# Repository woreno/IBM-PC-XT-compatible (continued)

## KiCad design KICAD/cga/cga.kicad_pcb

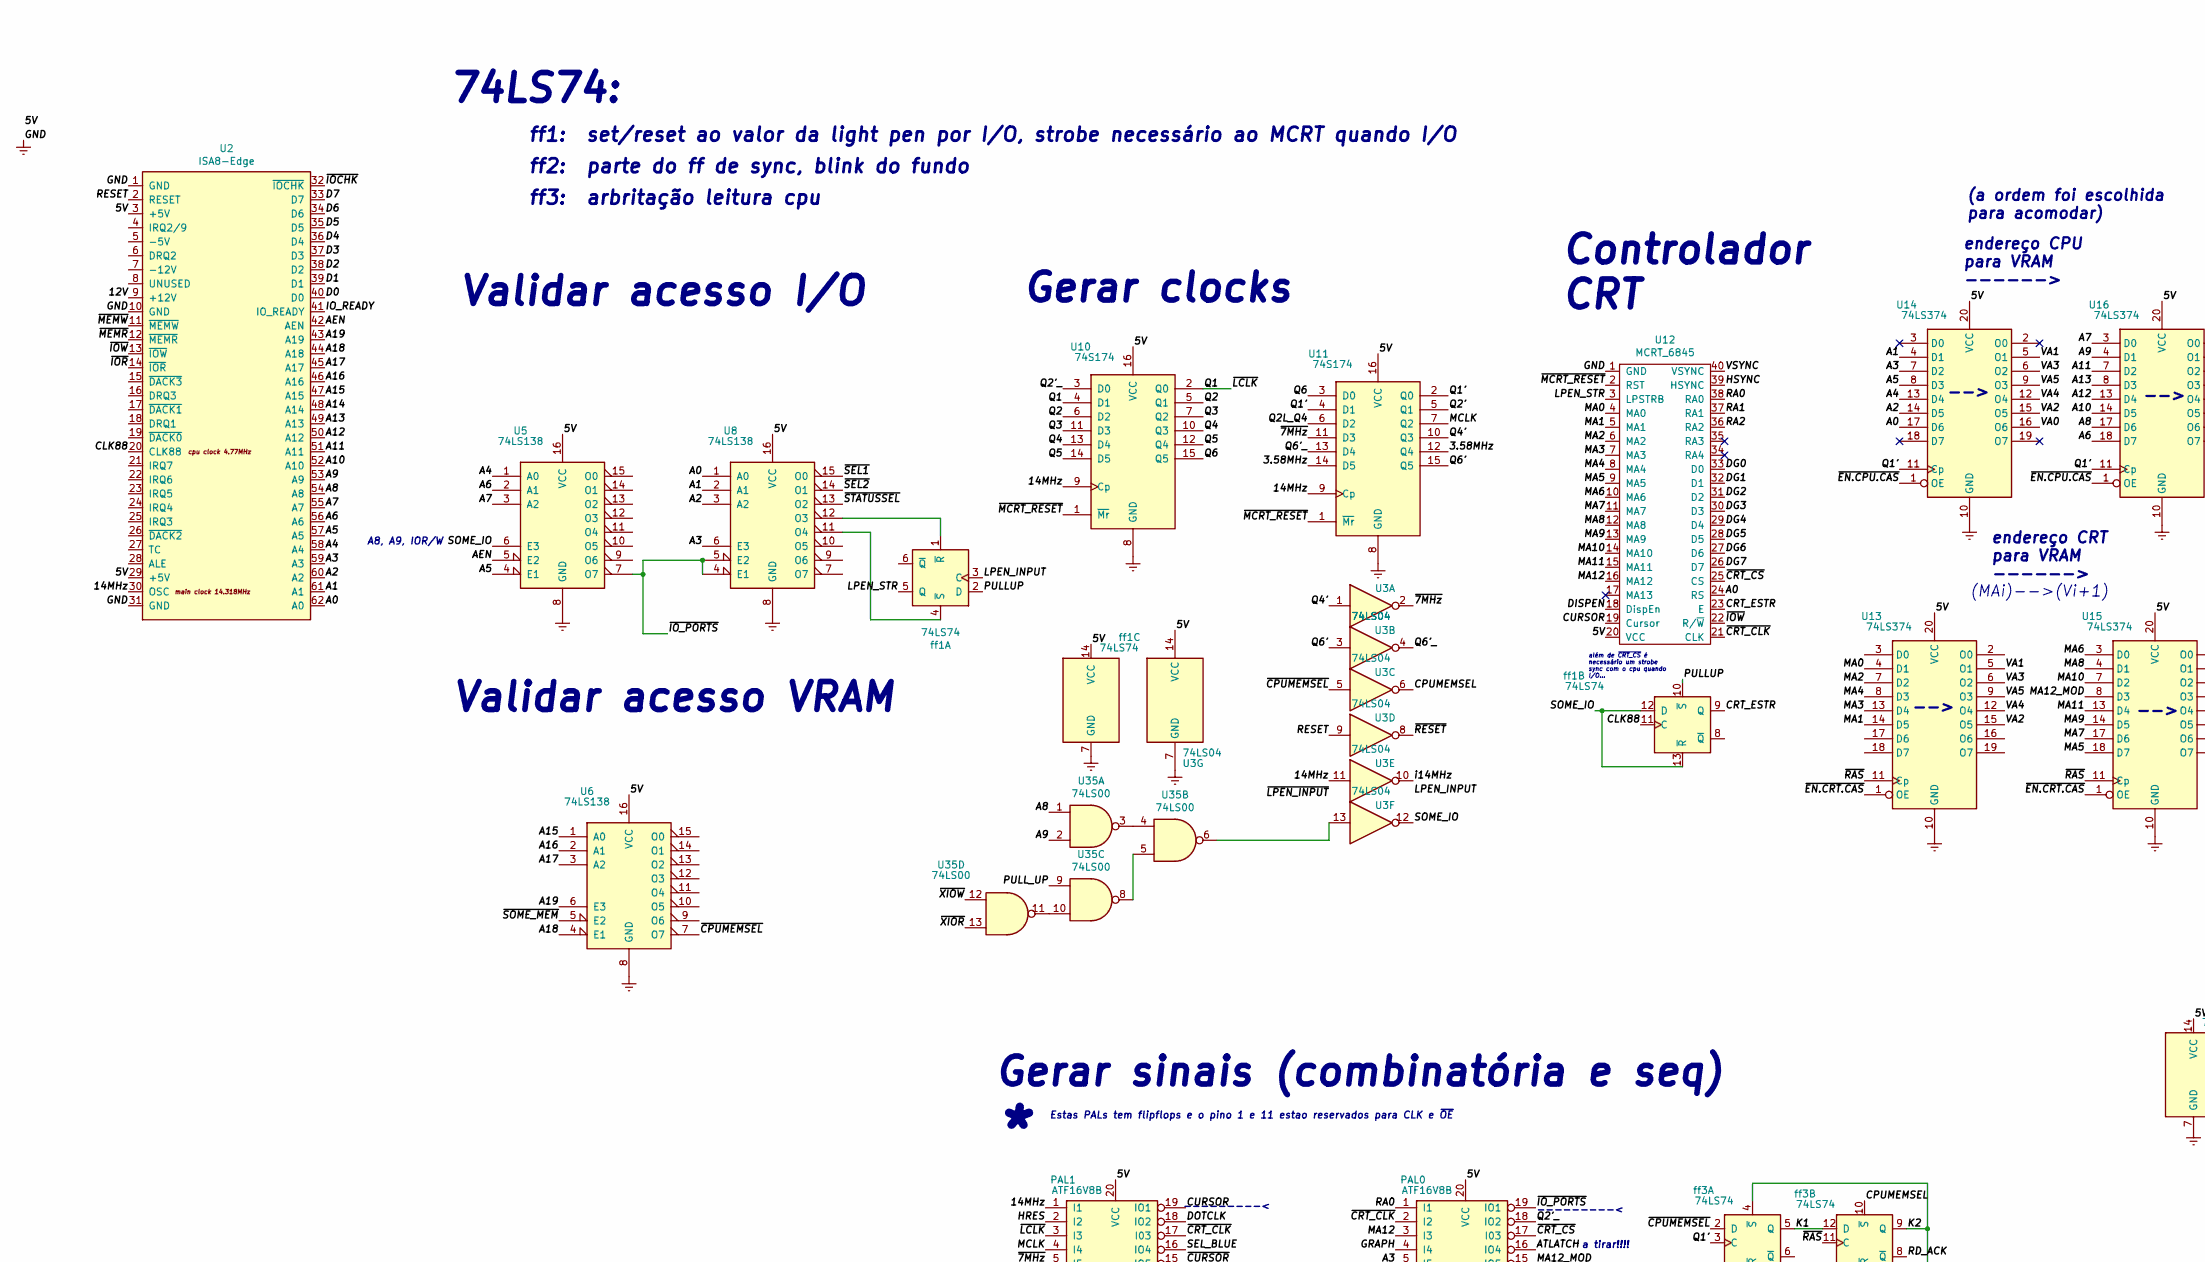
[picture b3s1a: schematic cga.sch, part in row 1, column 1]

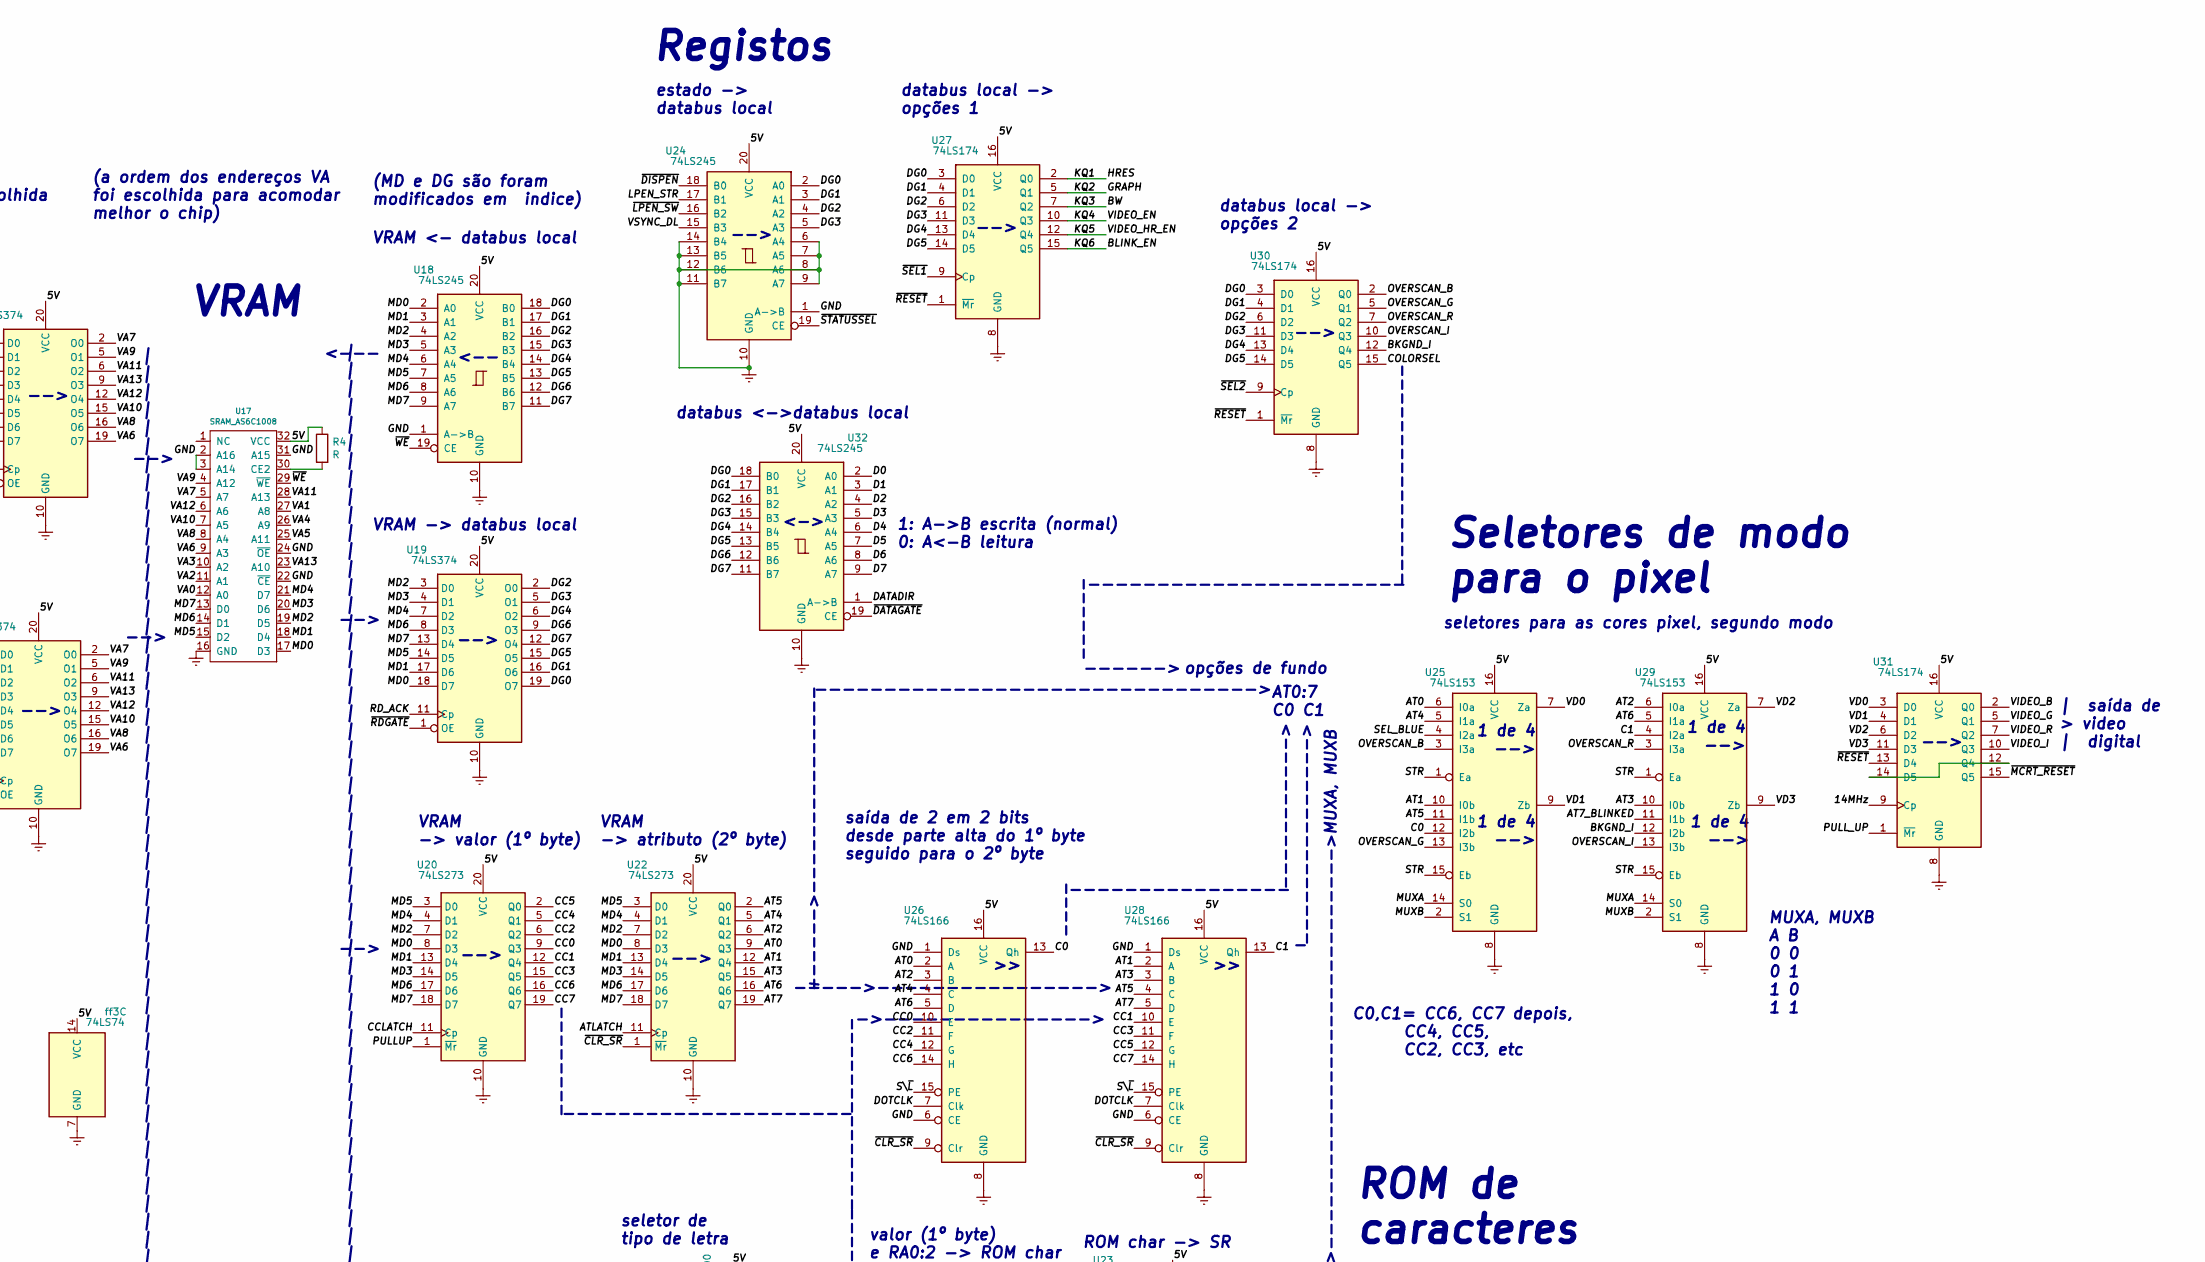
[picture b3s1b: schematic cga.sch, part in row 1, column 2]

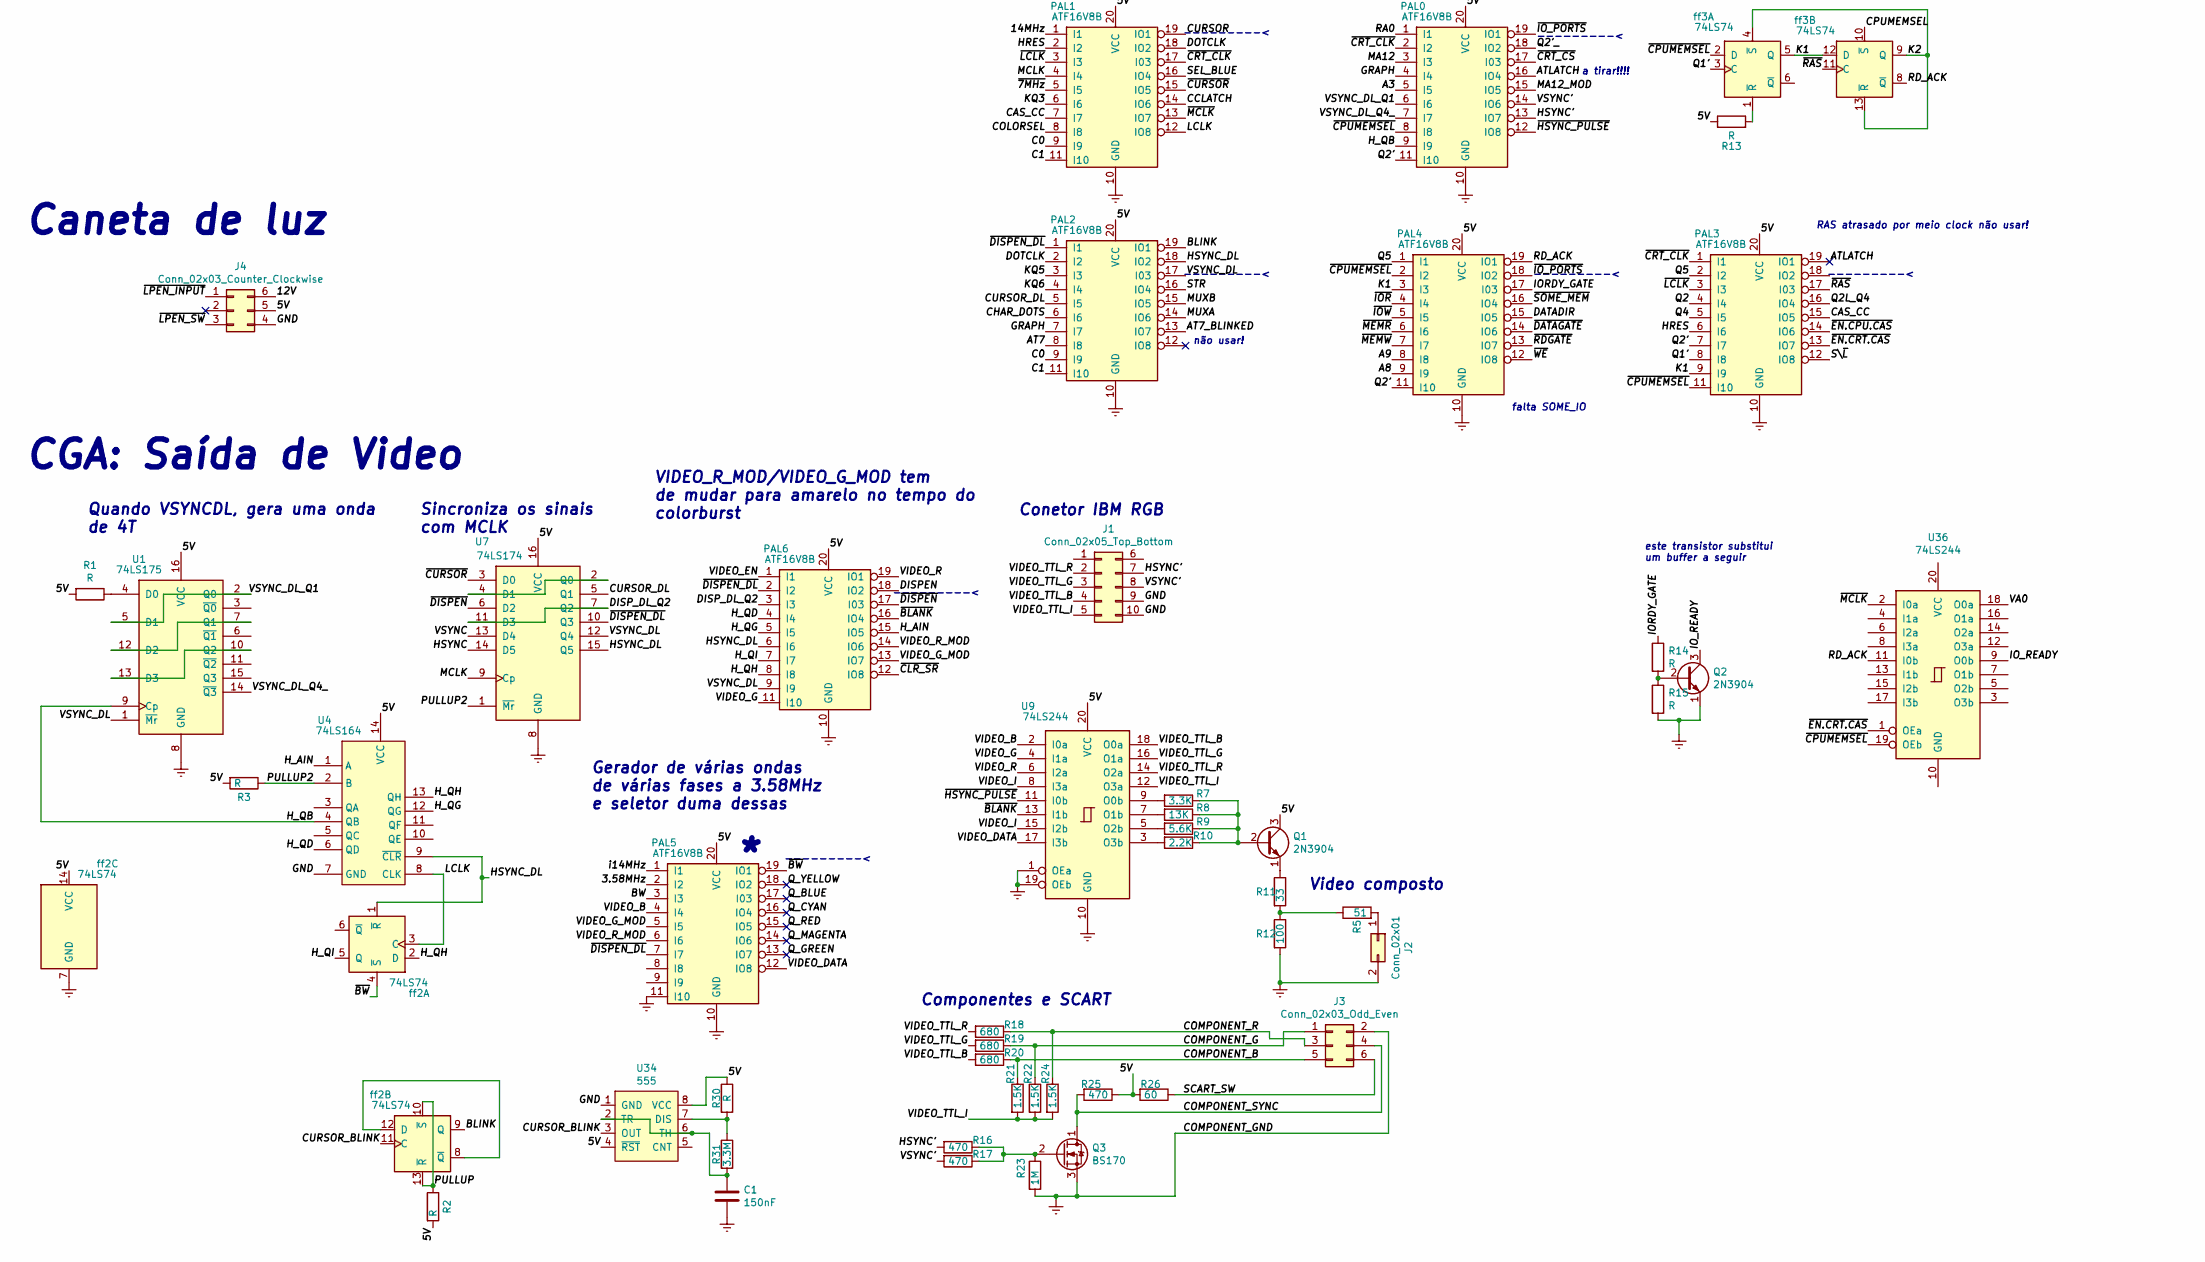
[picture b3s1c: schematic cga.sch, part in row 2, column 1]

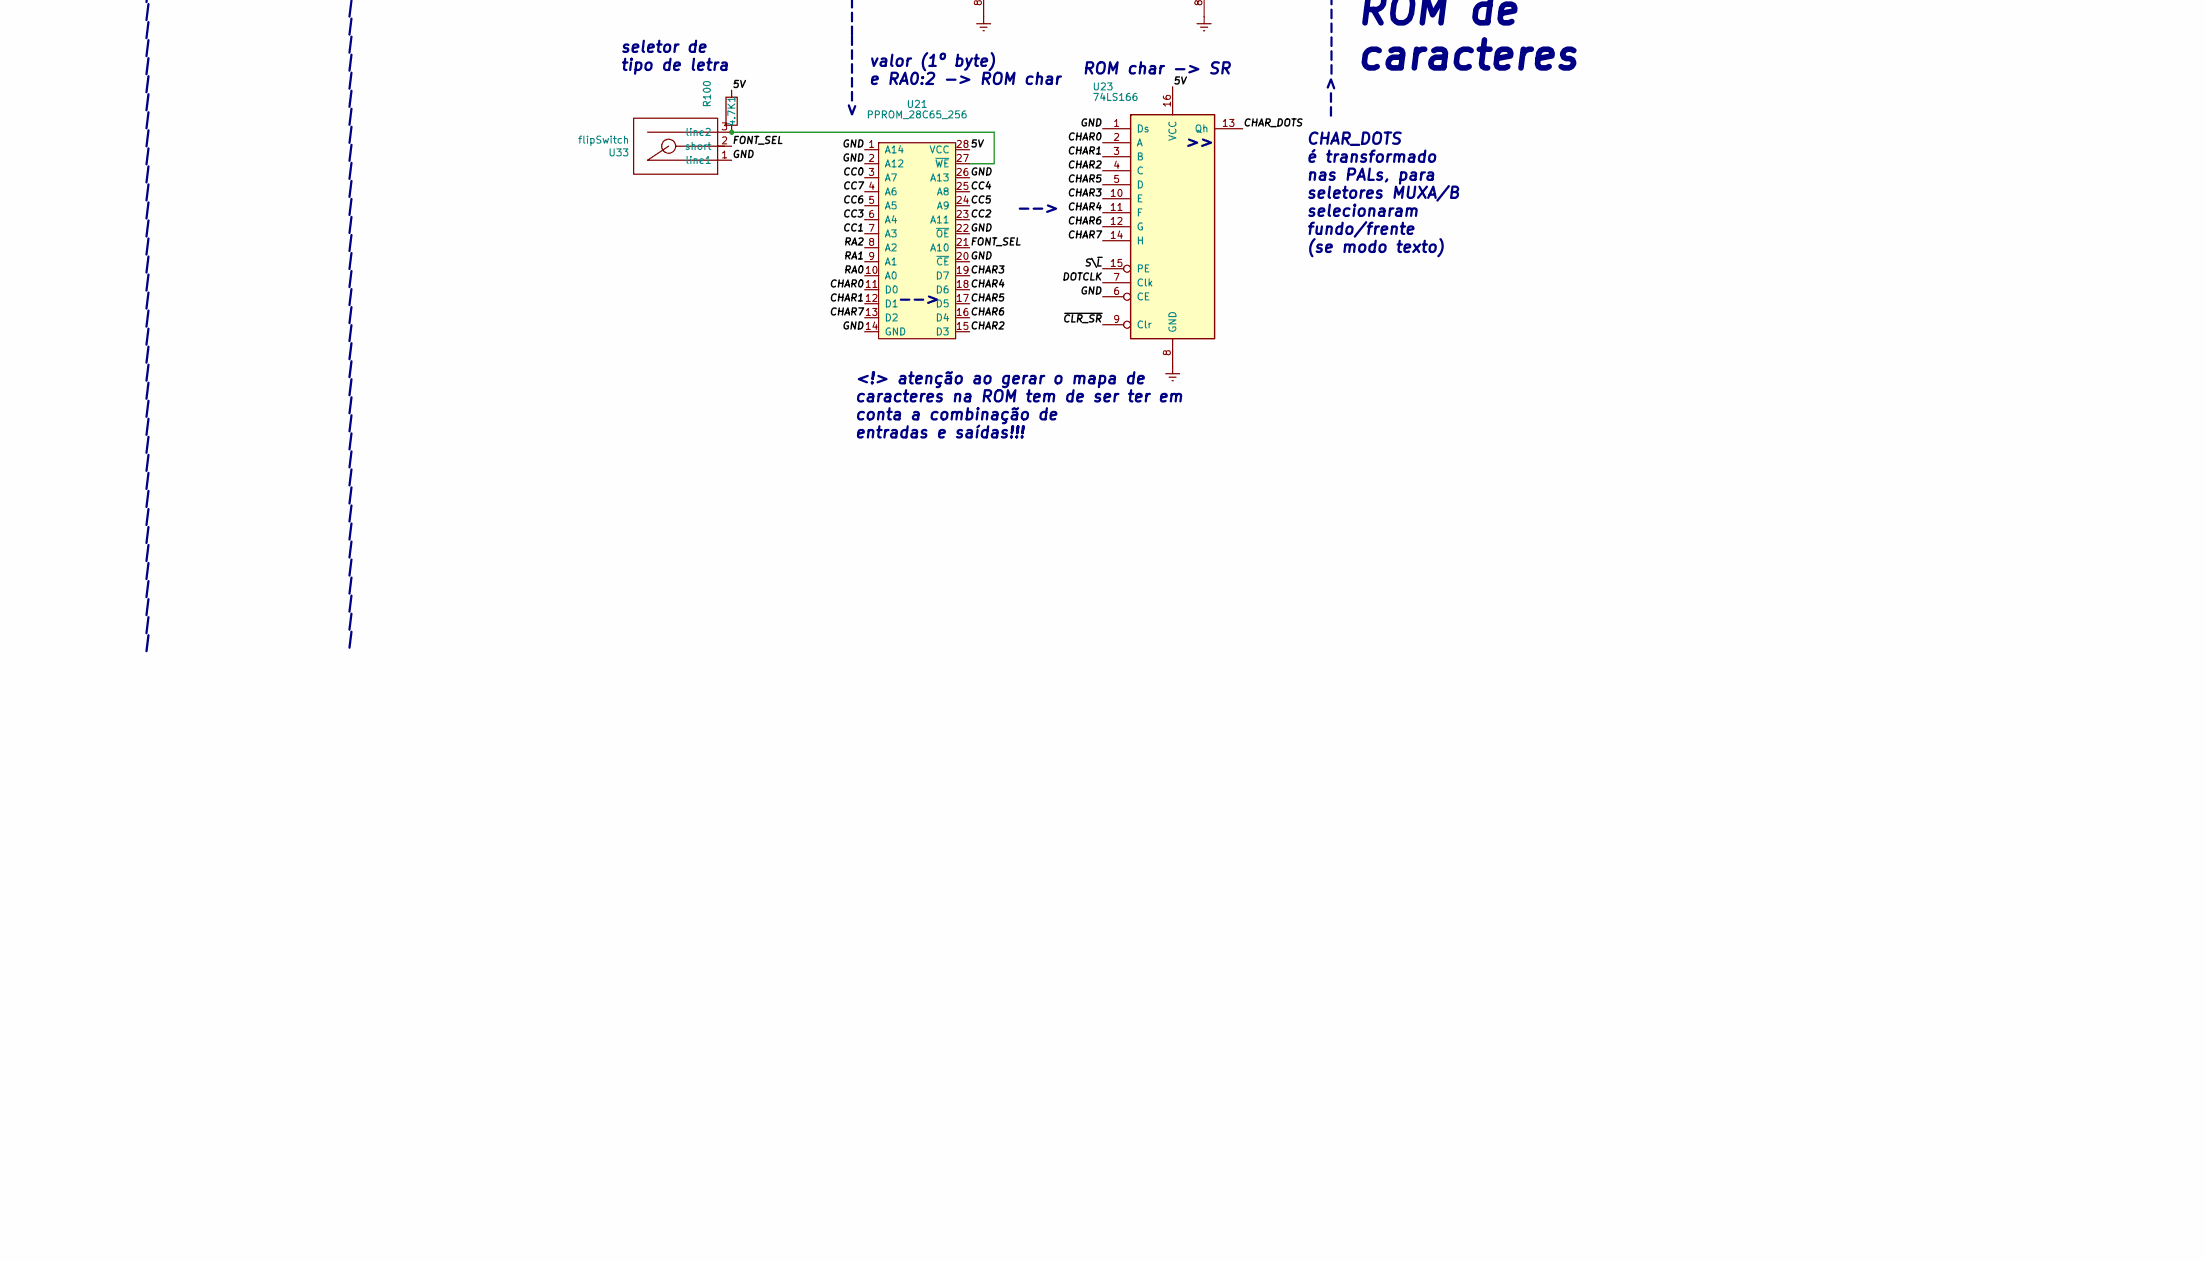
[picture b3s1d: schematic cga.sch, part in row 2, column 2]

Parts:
4.7K1: R100; standard_2pins
C1: 150nF; standard_2pins_half
J1: Conn_02x05_Top_Bottom; conetor_2x05_P2.54_toDB9
J2: Conn_02x01; jumper_set_1
J3: Conn_02x03_Odd_Even; jumper_set_3
J4: Conn_02x03_Counter_Clockwise; jumper_set_3
PAL0, PAL1, PAL2, PAL3, PAL4, PAL5, PAL6: ATF16V8B; standard_DIP_20pins_thin_body
Q1, Q2: 2N3904; TO-92_Inline
Q3: BS170; TO-92_Inline
R1, R2, R3, R4, R13, R14, R15, R30: R; standard_2pins
R5: 51; standard_2pins
R7: 3.3K; standard_2pins
R8: 13K; standard_2pins
R9: 5.6K; standard_2pins
R10: 2.2K; standard_2pins
R11: 33; standard_2pins
R12: 100; standard_2pins
R16, R17, R25: 470; standard_2pins
R18, R19, R20: 680; standard_2pins
R21, R22, R24: 1.5K; standard_2pins
R23: 1M; standard_2pins
R26: 60; standard_2pins
R31: 3.3M; standard_2pins
U1: 74LS175; standard_DIP_16OvalPins
U2: ISA8-Edge; ISA_8bit_edge
U3: 74LS04; standard_DIP_14OvalPins
U4: 74LS164; standard_DIP_14OvalPins
U5, U6, U8: 74LS138; standard_DIP_16OvalPins
U7, U27, U30, U31: 74LS174; standard_DIP_16OvalPins
U9, U36: 74LS244; standard_DIP_20pins_thin_body
U10, U11: 74S174; standard_DIP_16OvalPins
U12: MCRT_6845; standard_DIP_40pins_doubleBody_thinpins
U13, U14, U15, U16, U19: 74LS374; standard_DIP_20pins_thin_body
U17: SRAM_AS6C1008; standard_DIP_32pins_thin_doubleBody
U18, U24, U32: 74LS245; standard_DIP_20pins_thin_body
U20, U22: 74LS273; standard_DIP_20pins_thin_body
U21: PPROM_28C65_256; standard_DIP_28pins_thin_doubleBody
U23, U26, U28: 74LS166; standard_DIP_16OvalPins
U25, U29: 74LS153; standard_DIP_16OvalPins
U33: flipSwitch; mini_flipswitch2.54
U34: 555; standard_DIP_8pins
U35: 74LS00; standard_DIP_14OvalPins
ff1, ff2, ff3: 74LS74; standard_DIP_14OvalPins

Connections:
/3.58MHz: PAL5.2 (I2), U11.12 (Q4), U11.14 (D5)
/5V: 4.7K1.1, J4.5, PAL0.20 (VCC), PAL1.20 (VCC), PAL2.20 (VCC), PAL3.20 (VCC), PAL4.20 (VCC), PAL5.20 (VCC), PAL6.20 (VCC), Q1.3 (C), R1.2, R2.2, R3.2, R4.1, R13.1, R25.1, R26.2, R30.1, U1.16 (VCC), U2.3 (+5V), U2.29 (+5V), U3.14 (VCC), U4.14 (VCC), U5.16 (VCC), U6.16 (VCC), U7.16 (VCC), U8.16 (VCC), U9.20 (VCC), U10.16 (VCC), U11.16 (VCC), U12.20 (VCC), U13.20 (VCC), U14.20 (VCC), U15.20 (VCC), U16.20 (VCC), U17.32 (VCC), U18.20 (VCC), U19.20 (VCC), U20.20 (VCC), U21.28 (VCC), U22.20 (VCC), U23.16 (VCC), U24.20 (VCC), U25.16 (VCC), U26.16 (VCC), U27.16 (VCC), U28.16 (VCC), U29.16 (VCC), U30.16 (VCC), U31.16 (VCC), U32.20 (VCC), U34.4 (~RST), U34.8 (VCC), ff1.14 (VCC), ff2.14 (VCC), ff3.14 (VCC); also elsewhere on the board
/12V: J4.6, U2.9 (+12V)
/14MHz: PAL1.1 (I1), U2.30 (OSC), U3.11, U10.9 (Cp), U11.9 (Cp), U31.9 (Cp)
/A0: U2.62 (A0), U8.1 (A0), U12.24 (RS), U14.17 (D6)
/A1: U2.61 (A1), U8.2 (A1), U14.4 (D1)
/A2: U2.60 (A2), U8.3 (A2), U14.14 (D5)
/A3: PAL0.5 (I5), U2.59 (A3), U8.6 (E3), U14.7 (D2)
/A4: U2.58 (A4), U5.1 (A0), U14.13 (D4)
/A5: U2.57 (A5), U5.4 (E1), U14.8 (D3)
/A6: U2.56 (A6), U5.2 (A1), U16.18 (D7)
/A7: U2.55 (A7), U5.3 (A2), U16.3 (D0)
/A8: PAL4.9 (I9), U2.54 (A8), U16.17 (D6), U35.1
/A9: PAL4.8 (I8), U2.53 (A9), U16.4 (D1), U35.2
/A10: U2.52 (A10), U16.14 (D5)
/A11: U2.51 (A11), U16.7 (D2)
/A12: U2.50 (A12), U16.13 (D4)
/A13: U2.49 (A13), U16.8 (D3)
/A14: U2.48 (A14)
/A15: U2.47 (A15), U6.1 (A0)
/A16: U2.46 (A16), U6.2 (A1)
/A17: U2.45 (A17), U6.3 (A2)
/A18: U2.44 (A18), U6.4 (E1)
/A19: U2.43 (A19), U6.6 (E3)
/AEN: U2.42 (AEN), U5.5 (E2)
/AT0: U22.9 (Q3), U25.6 (I0a), U26.2 (A)
/AT1: U22.12 (Q4), U25.10 (I0b), U28.2 (A)
/AT2: U22.6 (Q2), U26.3 (B), U29.6 (I0a)
/AT3: U22.15 (Q5), U28.3 (B), U29.10 (I0b)
/AT4: U22.5 (Q1), U25.5 (I1a), U26.4 (C)
/AT5: U22.2 (Q0), U25.11 (I1b), U28.4 (C)
/AT6: U22.16 (Q6), U26.5 (D), U29.5 (I1a)
/AT7: PAL2.8 (I8), U22.19 (Q7), U28.5 (D)
/AT7_BLINKED: PAL2.13 (IO7), U29.11 (I1b)
/ATLATCH: PAL0.16 (IO4), PAL3.19 (IO1), U22.11 (Cp)
/BKGND_I: U29.12 (I2b), U30.12 (Q4)
/BLINK: PAL2.19 (IO1), ff2.9 (Q)
/BLINK_EN: PAL2.4 (I4), U27.15 (Q5)
/BW: PAL1.6 (I6), PAL5.3 (I3), U27.7 (Q2)
/C0: PAL1.9 (I9), PAL2.9 (I9), U25.12 (I2b), U26.13 (Qh)
/C1: PAL1.11 (I10), PAL2.11 (I10), U28.13 (Qh), U29.4 (I2a)
/CAS_CC: PAL1.7 (I7), PAL3.15 (IO5)
/CC0: U20.9 (Q3), U21.3 (A7), U26.10 (E)
/CC1: U20.12 (Q4), U21.7 (A3), U28.10 (E)
/CC2: U20.6 (Q2), U21.23 (A11), U26.11 (F)
/CC3: U20.15 (Q5), U21.6 (A4), U28.11 (F)
/CC4: U20.5 (Q1), U21.25 (A8), U26.12 (G)
/CC5: U20.2 (Q0), U21.24 (A9), U28.12 (G)
/CC6: U20.16 (Q6), U21.5 (A5), U26.14 (H)
/CC7: U20.19 (Q7), U21.4 (A6), U28.14 (H)
/CCLATCH: PAL1.14 (IO6), U20.11 (Cp)
/CHAR0: U21.11 (D0), U23.2 (A)
/CHAR1: U21.12 (D1), U23.3 (B)
/CHAR2: U21.15 (D3), U23.4 (C)
/CHAR3: U21.19 (D7), U23.10 (E)
/CHAR4: U21.18 (D6), U23.11 (F)
/CHAR5: U21.17 (D5), U23.5 (D)
/CHAR6: U21.16 (D4), U23.12 (G)
/CHAR7: U21.13 (D2), U23.14 (H)
/CHAR_DOTS: PAL2.6 (I6), U23.13 (Qh)
/CLK88: U2.20 (CLK88), ff1.11 (C)
/COLORSEL: PAL1.8 (I8), U30.15 (Q5)
/COMPONENT_B: J3.5, R20.1, R21.1
/COMPONENT_G: J3.1, R19.1, R22.1
/COMPONENT_R: J3.3, R18.1, R24.1
/COMPONENT_SYNC: J3.4, Q3.1 (D), R25.2
/CPUMEMSEL: U3.6, ff3.10 (~S)
/CRT_ESTR: U12.23 (E), ff1.9 (Q)
/CURSOR: PAL1.19 (IO1), U12.19 (Cursor)
/CURSOR_BLINK: U34.3 (OUT), ff2.11 (C)
/CURSOR_DL: PAL2.5 (I5), U7.5 (Q1)
/D0: U2.40 (D0), U32.2 (A0)
/D1: U2.39 (D1), U32.3 (A1)
/D2: U2.38 (D2), U32.4 (A2)
/D3: U2.37 (D3), U32.5 (A3)
/D4: U2.36 (D4), U32.6 (A4)
/D5: U2.35 (D5), U32.7 (A5)
/D6: U2.34 (D6), U32.8 (A6)
/D7: U2.33 (D7), U32.9 (A7)
/DATADIR: PAL4.15 (IO5), U32.1 (A->B)
/DG0: U12.33 (D0), U18.18 (B0), U19.19 (O7), U24.2 (A0), U27.3 (D0), U30.3 (D0), U32.18 (B0)
/DG1: U12.32 (D1), U18.17 (B1), U19.16 (O6), U24.3 (A1), U27.4 (D1), U30.4 (D1), U32.17 (B1)
/DG2: U12.31 (D2), U18.16 (B2), U19.2 (O0), U24.4 (A2), U27.6 (D2), U30.6 (D2), U32.16 (B2)
/DG3: U12.30 (D3), U18.15 (B3), U19.5 (O1), U24.5 (A3), U27.11 (D3), U30.11 (D3), U32.15 (B3)
/DG4: U12.29 (D4), U18.14 (B4), U19.6 (O2), U27.13 (D4), U30.13 (D4), U32.14 (B4)
/DG5: U12.28 (D5), U18.13 (B5), U19.15 (O5), U27.14 (D5), U30.14 (D5), U32.13 (B5)
/DG6: U12.27 (D6), U18.12 (B6), U19.9 (O3), U32.12 (B6)
/DG7: U12.26 (D7), U18.11 (B7), U19.12 (O4), U32.11 (B7)
/DISPEN: PAL6.18 (IO2), U12.18 (DispEn)
/DISP_DL_Q2: PAL6.3 (I3), U7.7 (Q2), U7.11 (D3)
/DOTCLK: PAL1.18 (IO2), PAL2.2 (I2), U23.7 (Clk), U26.7 (Clk), U28.7 (Clk)
/FONT_SEL: U21.21 (A10), U33.2 (short)
/GRAPH: PAL0.4 (I4), PAL2.7 (I7), U27.5 (Q1)
/HRES: PAL1.2 (I2), PAL3.6 (I6), U27.2 (Q0)
/HSYNC: U7.14 (D5), U12.39 (HSYNC)
/HSYNC': J1.7, PAL0.13 (IO7), R16.2
/HSYNC_DL: PAL2.18 (IO2), PAL6.6 (I6), U4.9 (~CLR), U7.15 (Q5), ff2.1 (~R)
/H_AIN: PAL6.15 (IO5), U4.1 (A)
/H_QB: PAL0.9 (I9), U1.9 (Cp), U4.4 (QB)
/H_QD: PAL6.4 (I4), U4.6 (QD)
/H_QG: PAL6.5 (I5), U4.12 (QG)
/H_QH: PAL6.8 (I8), U4.13 (QH), ff2.2 (D)
/H_QI: PAL6.7 (I7), ff2.5 (Q)
/IORDY_GATE: PAL4.17 (I03), R14.1
/IO_READY: Q2.3 (C), U2.41 (IO_READY), U36.9 (O0b)
/K1: PAL3.9 (I9), PAL4.3 (I3), ff3.5 (Q), ff3.12 (D)
/K2: ff3.4 (~S), ff3.9 (Q), ff3.13 (~R)
/KQ4: PAL6.1 (I1), U27.10 (Q3)
/KQ5: PAL2.3 (I3), U27.12 (Q4)
/LCLK: PAL1.12 (IO8), U4.8 (CLK), ff2.3 (C)
/LPEN_INPUT: ff1.3 (C)
/LPEN_STR: U12.3 (LPSTRB), U24.17 (B1), ff1.5 (Q)
/MA0: U12.4 (MA0), U13.4 (D1)
/MA1: U12.5 (MA1), U13.14 (D5)
/MA2: U12.6 (MA2), U13.7 (D2)
/MA3: U12.7 (MA3), U13.13 (D4)
/MA4: U12.8 (MA4), U13.8 (D3)
/MA5: U12.9 (MA5), U15.18 (D7)
/MA6: U12.10 (MA6), U15.3 (D0)
/MA7: U12.11 (MA7), U15.17 (D6)
/MA8: U12.12 (MA8), U15.4 (D1)
/MA9: U12.13 (MA9), U15.14 (D5)
/MA10: U12.14 (MA10), U15.7 (D2)
/MA11: U12.15 (MA11), U15.13 (D4)
/MA12: PAL0.3 (I3), U12.16 (MA12)
/MA12_MOD: PAL0.15 (IO5), U15.8 (D3)
/MCLK: PAL1.4 (I4), U7.9 (Cp), U11.7 (Q2)
/MD0: U17.17 (D3), U18.2 (A0), U19.18 (D7), U20.8 (D3), U22.8 (D3)
/MD1: U17.18 (D4), U18.3 (A1), U19.17 (D6), U20.13 (D4), U22.13 (D4)
/MD2: U17.19 (D5), U18.4 (A2), U19.3 (D0), U20.7 (D2), U22.7 (D2)
/MD3: U17.20 (D6), U18.5 (A3), U19.4 (D1), U20.14 (D5), U22.14 (D5)
/MD4: U17.21 (D7), U18.6 (A4), U19.7 (D2), U20.4 (D1), U22.4 (D1)
/MD5: U17.15 (D2), U18.7 (A5), U19.14 (D5), U20.3 (D0), U22.3 (D0)
/MD6: U17.14 (D1), U18.8 (A6), U19.8 (D3), U20.17 (D6), U22.17 (D6)
/MD7: U17.13 (D0), U18.9 (A7), U19.13 (D4), U20.18 (D7), U22.18 (D7)
/MUXA: PAL2.14 (IO6), U25.14 (S0), U29.14 (S0)
/MUXB: PAL2.15 (IO5), U25.2 (S1), U29.2 (S1)
/OVERSCAN_B: U25.3 (I3a), U30.2 (Q0)
/OVERSCAN_G: U25.13 (I3b), U30.5 (Q1)
/OVERSCAN_I: U29.13 (I3b), U30.10 (Q3)
/OVERSCAN_R: U29.3 (I3a), U30.7 (Q2)
/PULLUP: R2.1, U20.1 (~Mr), ff1.2 (D), ff1.10 (~S), ff2.10 (~S), ff2.13 (~R)
/PULLUP2: R3.1, U4.2 (B), U7.1 (~Mr)
/PULL_UP: U31.1 (~Mr), U35.9
/Q1: PAL1.3 (I3), PAL3.3 (I3), U10.2 (Q0), U10.4 (D1)
/Q1': PAL3.8 (I8), U11.2 (Q0), U11.4 (D1), U14.11 (Cp), U16.11 (Cp), ff3.3 (C)
/Q2: PAL3.4 (I4), U10.5 (Q1), U10.6 (D2)
/Q2': PAL0.11 (I10), PAL3.7 (I7), PAL4.11 (I10), U11.5 (Q1)
/Q2'_: PAL0.18 (IO2), U10.3 (D0)
/Q2L_Q4: PAL3.16 (IO4), U11.6 (D2)
/Q3: U10.7 (Q2), U10.11 (D3)
/Q4: PAL3.5 (I5), U10.10 (Q3), U10.13 (D4)
/Q4': U3.1, U11.10 (Q3)
/Q5: PAL3.2 (I2), PAL4.1 (I1), U10.12 (Q4), U10.14 (D5)
/Q6: U10.15 (Q5), U11.3 (D0)
/Q6': U3.3, U11.15 (Q5)
/Q6'_: U3.4, U11.13 (D4)
/Q_BLUE: PAL5.17 (I03)
/Q_CYAN: PAL5.16 (IO4)
/Q_GREEN: PAL5.13 (IO7)
/Q_MAGENTA: PAL5.14 (IO6)
/Q_RED: PAL5.15 (IO5)
/Q_YELLOW: PAL5.18 (IO2)
/RA0: PAL0.1 (I1), U12.38 (RA0), U21.10 (A0)
/RA1: U12.37 (RA1), U21.9 (A1)
/RA2: U12.36 (RA2), U21.8 (A2)
/RD_ACK: PAL4.19 (IO1), U19.11 (Cp), U36.11 (I0b), ff3.8 (~Q)
/RESET: U2.2 (RESET), U3.9
/SCART_SW: J3.6, R26.1
/SEL_BLUE: PAL1.16 (IO4), U25.4 (I2a)
/SOME_IO: U3.12, U5.6 (E3), ff1.12 (D), ff1.13 (~R)
/STR: PAL2.16 (IO4), U25.1 (Ea), U25.15 (Eb), U29.1 (Ea), U29.15 (Eb)
/S\~L: PAL3.12 (IO8), U23.15 (PE), U26.15 (PE), U28.15 (PE)
/VA0: U14.16 (O6), U17.12 (A0), U36.18 (O0a); also elsewhere on the board
/VA1: U13.5 (O1), U14.5 (O1), U17.27 (A8)
/VA2: U13.15 (O5), U14.15 (O5), U17.11 (A1)
/VA3: U13.6 (O2), U14.6 (O2), U17.10 (A2)
/VA4: U13.12 (O4), U14.12 (O4), U17.26 (A9)
/VA5: U13.9 (O3), U14.9 (O3), U17.25 (A11)
/VA6: U15.19 (O7), U16.19 (O7), U17.9 (A3)
/VA7: U15.2 (O0), U16.2 (O0), U17.5 (A7)
/VA8: U15.16 (O6), U16.16 (O6), U17.8 (A4)
/VA9: U15.5 (O1), U16.5 (O1), U17.4 (A12)
/VA10: U15.15 (O5), U16.15 (O5), U17.7 (A5)
/VA11: U15.6 (O2), U16.6 (O2), U17.28 (A13)
/VA12: U15.12 (O4), U16.12 (O4), U17.6 (A6)
/VA13: U15.9 (O3), U16.9 (O3), U17.23 (A10)
/VD0: U25.7 (Za), U31.3 (D0)
/VD1: U25.9 (Zb), U31.4 (D1)
/VD2: U29.7 (Za), U31.6 (D2)
/VD3: U29.9 (Zb), U31.11 (D3)
/VIDEO_B: PAL5.4 (I4), U9.2 (I0a), U31.2 (Q0)
/VIDEO_DATA: PAL5.12 (IO8), U9.17 (I3b)
/VIDEO_G: PAL6.11 (I10), U9.4 (I1a), U31.5 (Q1)
/VIDEO_G_MOD: PAL5.5 (I5), PAL6.13 (IO7)
/VIDEO_I: U9.8 (I3a), U9.15 (I2b), U31.10 (Q3)
/VIDEO_R: PAL6.19 (IO1), U9.6 (I2a), U31.7 (Q2)
/VIDEO_R_MOD: PAL5.6 (I6), PAL6.14 (IO6)
/VIDEO_TTL_B: J1.4, R20.2, U9.18 (O0a)
/VIDEO_TTL_G: J1.3, R19.2, U9.16 (O1a)
/VIDEO_TTL_I: J1.5, R21.2, R22.2, R24.2, U9.12 (O3a)
/VIDEO_TTL_R: J1.2, R18.2, U9.14 (O2a)
/VSYNC: U7.13 (D4), U12.40 (VSYNC)
/VSYNC': J1.8, PAL0.14 (IO6), R17.2
/VSYNC_DL: PAL2.17 (I03), PAL6.9 (I9), U1.1 (~Mr), U7.12 (Q4), U24.15 (B3)
/VSYNC_DL_Q1: PAL0.6 (I6), U1.2 (Q0), U1.5 (D1)
/VSYNC_DL_Q4_: PAL0.7 (I7), U1.14 (~Q3)
/i14MHz: PAL5.1 (I1), U3.10
/~7MHz: PAL1.5 (I5), U3.2, U11.11 (D3)
/~BLANK: PAL6.16 (IO4), U9.13 (I1b)
/~BW: PAL5.19 (IO1), ff2.4 (~S)
/~CLR_SR: PAL6.12 (IO8), U22.1 (~Mr), U23.9 (Clr), U26.9 (Clr), U28.9 (Clr)
/~CPUMEMSEL: PAL0.8 (I8), PAL3.11 (I10), PAL4.2 (I2), U3.5, U6.7 (O7), U36.19 (OEb), ff3.2 (D)
/~CRT_CLK: PAL0.2 (I2), PAL1.17 (I03), PAL3.1 (I1), U12.21 (CLK)
/~CRT_CS: PAL0.17 (I03), U12.25 (CS)
/~CURSOR: PAL1.15 (IO5), U7.3 (D0)
/~DATAGATE: PAL4.14 (IO6), U32.19 (CE)
/~DISPEN: PAL6.17 (I03), U7.6 (D2), U24.18 (B0)
/~DISPEN_DL: PAL2.1 (I1), PAL5.7 (I7), PAL6.2 (I2), U7.10 (Q3)
/~EN.CPU.CAS: PAL3.14 (IO6), U14.1 (OE), U16.1 (OE)
/~EN.CRT.CAS: PAL3.13 (IO7), U13.1 (OE), U15.1 (OE), U36.1 (OEa); also elsewhere on the board
/~HSYNC_PULSE: PAL0.12 (IO8), U9.11 (I0b)
/~IOCHK: U2.32 (~IOCHK)
/~IOR: PAL4.4 (I4), U2.14 (~IOR)
/~IOW: PAL4.5 (I5), U2.13 (~IOW), U12.22 (R/~W)
/~IO_PORTS: PAL0.19 (IO1), PAL4.18 (IO2), U5.7 (O7), U8.4 (E1), U8.5 (E2)
/~LPEN_INPUT: J4.1
/~LPEN_SW: J4.3, U24.16 (B2)
/~MCLK: PAL1.13 (IO7), U36.2 (I0a); also elsewhere on the board
/~MEMR: PAL4.6 (I6), U2.12 (~MEMR)
/~MEMW: PAL4.7 (I7), U2.11 (~MEMW)
/~RAS: PAL3.17 (I03), U13.11 (Cp), U15.11 (Cp), ff3.11 (C)
/~RDGATE: PAL4.13 (IO7), U19.1 (OE)
/~RESET: U3.8, U27.1 (~Mr), U30.1 (~Mr), U31.13 (D4)
/~RESET2: U10.1 (~Mr), U11.1 (~Mr), U12.2 (RST), U31.15 (Q5)
/~SEL1: U8.15 (O0), U27.9 (Cp)
/~SEL2: U8.14 (O1), U30.9 (Cp)
/~SOME_MEM: PAL4.16 (IO4), U6.5 (E2)
/~STATUSSEL: U8.13 (O2), U24.19 (CE)
/~WE: PAL4.12 (IO8), U17.29 (~WE), U18.19 (CE)
/~XIOR: U35.13
/~XIOW: U35.12
unnamed: 4.7K1.2, U21.27 (~WE), U33.3 (line2)
unnamed: C1.1, R31.2, U34.2 (TR), U34.6 (TH)
unnamed: J2.1, R5.2
unnamed: Q1.1 (E), R11.1
unnamed: Q1.2 (B), R7.1, R8.1, R9.1, R10.1
unnamed: Q2.2 (B), R14.2, R15.1
unnamed: Q3.2 (G), R16.1, R17.1, R23.1
unnamed: R1.1, U1.4 (D0)
unnamed: R4.2, U17.30 (CE2)
unnamed: R7.2, U9.9 (O0b)
unnamed: R8.2, U9.7 (O1b)
unnamed: R9.2, U9.5 (O2b)
unnamed: R10.2, U9.3 (O3b)
unnamed: R5.1, R11.2, R12.1
unnamed: R13.2, ff3.1 (~R)
unnamed: R30.2, R31.1, U34.7 (DIS)
unnamed: U1.10 (Q2), U1.13 (D3)
unnamed: U1.7 (Q1), U1.12 (D2)
unnamed: U3.13, U35.6
unnamed: U7.2 (Q0), U7.4 (D1)
unnamed: U8.11 (O4), ff1.4 (~S)
unnamed: U8.12 (O3), ff1.1 (~R)
unnamed: U31.12 (Q4), U31.14 (D5)
unnamed: U35.3, U35.4
unnamed: U35.5, U35.8
unnamed: U35.10, U35.11
unnamed: ff2.8 (~Q), ff2.12 (D)

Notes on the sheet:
Gerar clocks
Validar acesso I/O
Validar acesso VRAM
Controlador CRT
estado -> databus local
endereço CPU para VRAM ------>
VRAM -> databus local
VRAM <- databus local
VRAM
endereço CRT para VRAM ------>
VRAM -> valor (1º byte)
VRAM -> atributo (2º byte)
| | | | | | | | | | | | | | | | | | | | | | | | | | | | | | | | | | | | | | | | | | | | | | | | | | | | | | | | | | | | | | | | | | | | | | | | | | | | | | | | | |
valor (1º byte) e RA0:2 -> ROM char
ROM char -> SR
saída de 2 em 2 bits desde parte alta do 1º byte seguido para o 2º byte
seletores para as cores pixel, segundo modo
databus local -> opções 1
databus local -> opções 2
Gerar sinais (combinatória e seq)
Estas PALs tem flipflops e o pino 1 e 11 estao reservados para CLK e ~OE
(a ordem foi escolhida para acomodar)
(a ordem dos endereços VA foi escolhida para acomodar melhor o chip)
<!> atenção ao gerar o mapa de caracteres na ROM tem de ser ter em conta a combinação de entradas e saídas!!!
CGA: Saída de Video
Video composto
Conetor IBM RGB
Gerador de várias ondas de várias fases a 3.58MHz e seletor duma dessas
Quando VSYNCDL, gera uma onda de 4T
Componentes e SCART
Sincroniza os sinais com MCLK
VIDEO_R_MOD/VIDEO_G_MOD tem de mudar para amarelo no tempo do colorburst
seletor de tipo de letra
74LS74:
ff1: set/reset ao valor da light pen por I/O, strobe necessário ao MCRT quando I/O
ff2: parte do ff de sync, blink do fundo
ff3: arbritação leitura cpu
---------<
não usar!
RAS atrasado por meio clock não usar!

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
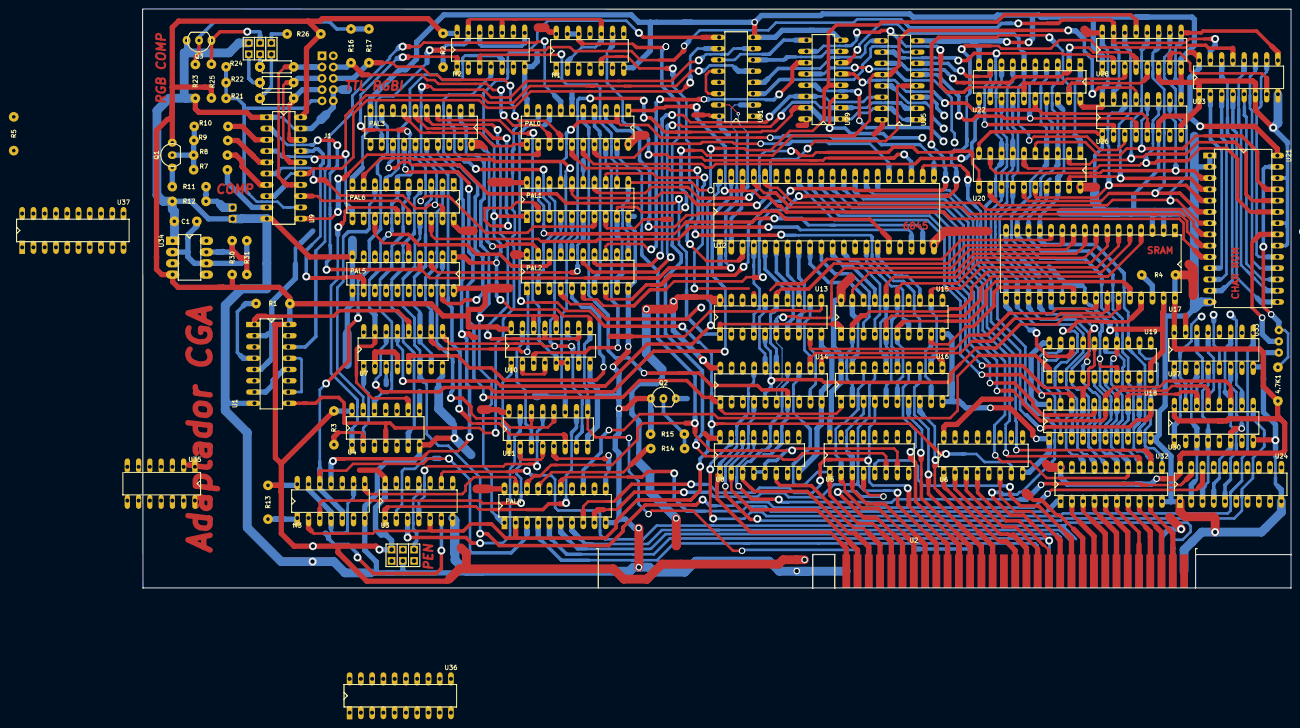
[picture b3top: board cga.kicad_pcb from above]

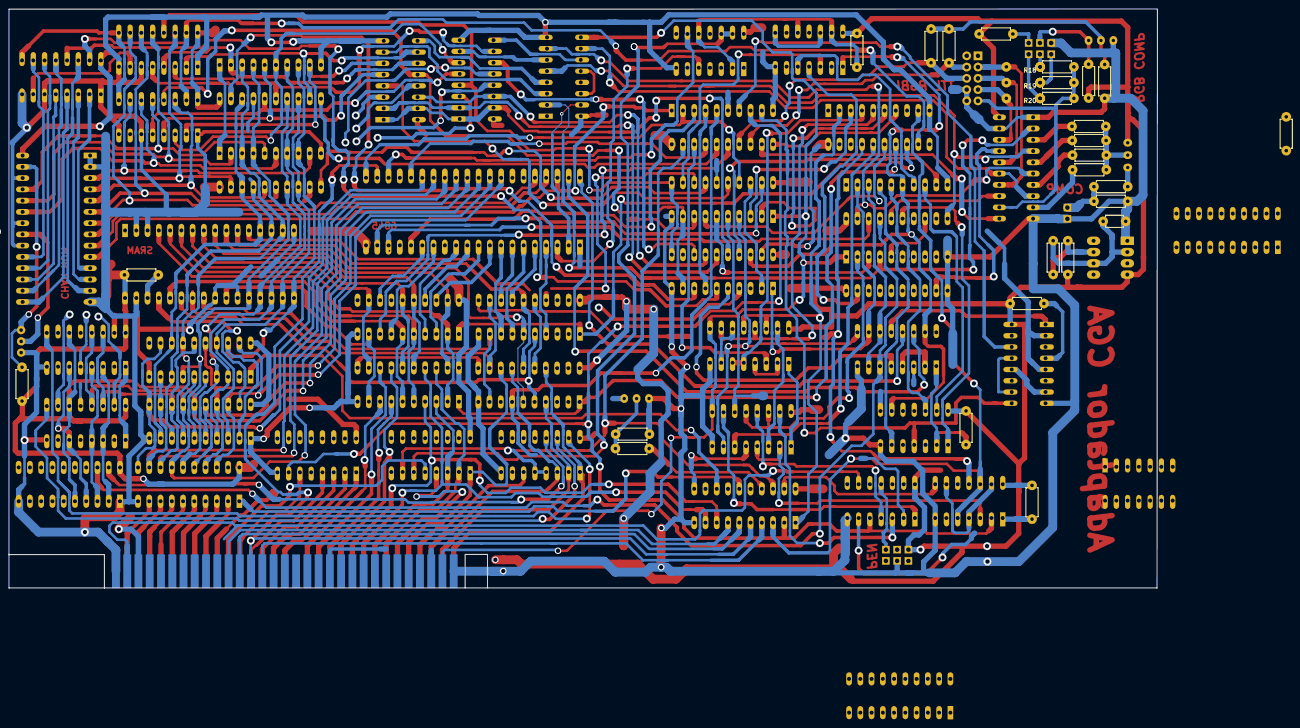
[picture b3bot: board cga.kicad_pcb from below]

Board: 2 copper layers, 259.1 x 130.6 mm, 83 parts (3 on the bottom side), 258 nets.

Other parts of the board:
U37: 74LS245; standard_DIP_20pins_thin_body

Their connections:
/5V: U37.20; also elsewhere on the board
/VA0: U37.2; also elsewhere on the board
/~EN.CRT.CAS: U37.19; also elsewhere on the board
/~MCLK: U37.18; also elsewhere on the board
